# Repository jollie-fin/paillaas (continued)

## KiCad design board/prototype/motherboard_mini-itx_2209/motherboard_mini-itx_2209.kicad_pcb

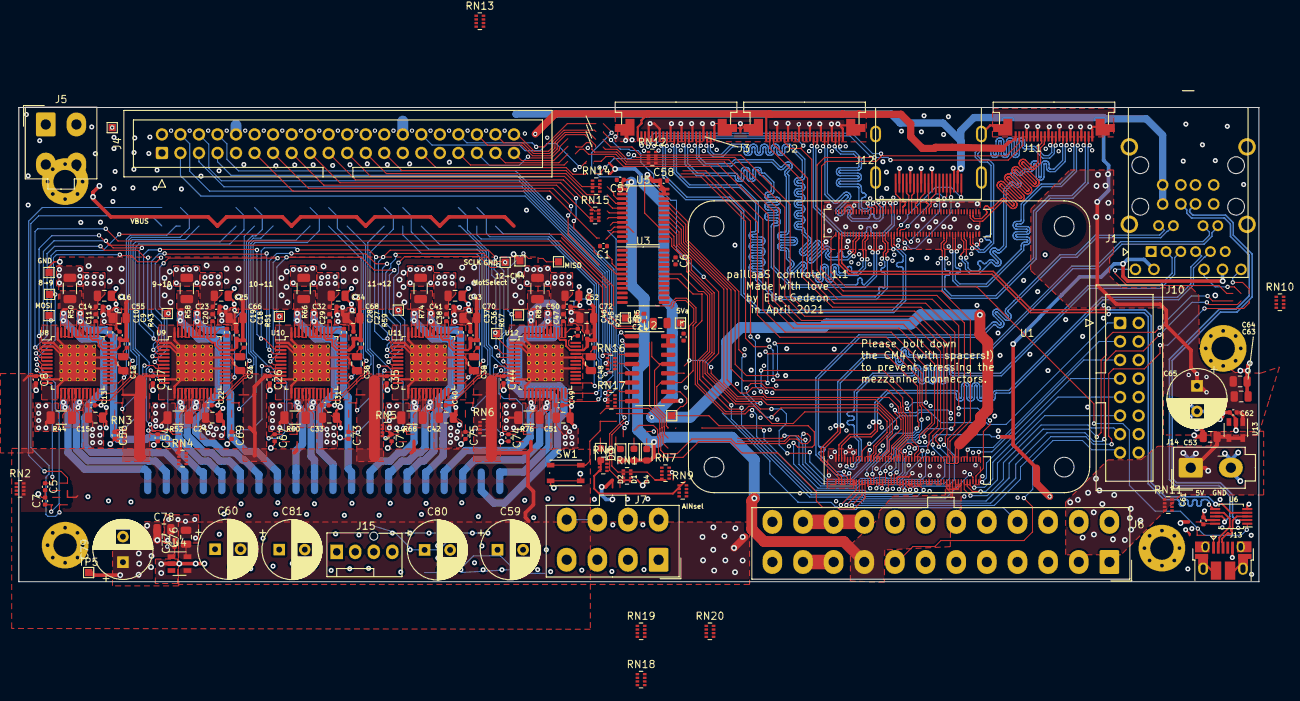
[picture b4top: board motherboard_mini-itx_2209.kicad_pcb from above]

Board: 4 copper layers, 170.0 x 65.0 mm, 167 parts (0 on the bottom side), 219 nets.

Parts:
C1, C2, C3, C6, C8, C9, C11, C13, C14, C17, C18, C20, C22, C23, C26, C27, C29, C31, C32, C35, C36, C38, C40, C41, C44, C45, C47, C49, C50, C57, C58, C61, C62, C77: 100n; C_0402_1005Metric
C4, C12, C15, C16, C21, C24, C25, C30, C33, C34, C39, C42, C43, C48, C51, C52, C53, C55, C63, C64, C66, C68, C70, C72, C76, C78: 10u; C_0805_2012Metric
C5, C7, C54, C56, C67, C69, C71, C73, C74, C75: 1n; C_0402_1005Metric
C10, C19, C28, C37, C46: 22n; C_0402_1005Metric
C59, C60, C65, C79, C80, C81: 100u; CP_Radial_D8.0mm_P3.50mm
D1, D2, D3, D4: RED; LED_0603_1608Metric
H1, H2, H3, H4: 4mm; MountingHole_3.2mm_M3_Pad_Via
J1: RJMG2310228A0ER
J2, J3, J11: Conn_01x22_MountingPin; SFV22R-1STBE1HLF
J4: Conn_02x20_Odd_Even; IDC-Header_2x20_P2.54mm_Vertical
J5: Conn_01x04_Female; Molex_Mini-Fit_Jr_5566-04A_2x02_P4.20mm_Vertical
J6: ATX24pin; Molex_Mini-Fit_Jr_5566-24A_2x12_P4.20mm_Vertical
J7: ATXP8; Molex_Mini-Fit_Jr_5566-08A_2x04_P4.20mm_Vertical
J10: Conn_02x08_Odd_Even; IDC-Header_2x08_P2.54mm_Vertical
J12: HDMI_A; HDMI_RAHHD19TR
J13: USB_B_Micro; USB_Micro-B_Amphenol_10103594-0001LF_Horizontal
J14: Conn_02x01; Molex_Mini-Fit_Jr_5566-02A_2x01_P4.20mm_Vertical
J15: Fan connector; FanPinHeader_1x04_P2.54mm_Vertical
R5, R43, R51, R59, R67, R75: 10; R_0402_1005Metric
R44, R50, R52, R58, R60, R66, R68, R74, R76, R82: 0R15; R_1206_3216Metric
RN1, RN2, RN3, RN4, RN5, RN6, RN7: 4x10k; R_Array_Concave_4x0402
RN8, RN9, RN10, RN11: 4x1k8; R_Array_Concave_4x0402
RN12, RN13, RN14, RN15, RN16, RN17: 4x150; R_Array_Concave_4x0402
RN18, RN19, RN20: 4x39; R_Array_Concave_4x0402
SW1: PTS526 SM15 SMTR2 LFS; SW_Push_1P1T_NO_Vertical_Wuerth_434133025816
TP1: 3V3a; TestPoint_Pad_1.0x1.0mm
TP2: AinSel; TestPoint_Pad_1.0x1.0mm
TP3, TP4, TP10: GND; TestPoint_Pad_1.0x1.0mm
TP5: 3V3bus; TestPoint_Pad_1.0x1.0mm
TP6: MISO; TestPoint_Pad_1.0x1.0mm
TP7: SCLK; TestPoint_Pad_1.0x1.0mm
TP8: MOSI; TestPoint_Pad_1.0x1.0mm
TP9: MotSel; TestPoint_Pad_1.0x1.0mm
TP11, TP13, TP15, TP17, TP19: Toright; TestPoint_Pad_1.0x1.0mm
TP12: 5Vbus; TestPoint_Pad_1.0x1.0mm
U1: Compute_Module_4_Functional; Raspberry-Pi-4-Compute-Module
U2: MCP3008; SOIC-16_3.9x9.9mm_P1.27mm
U3, U5: 74LVC4245A; TSSOP-24_4.4x7.8mm_P0.65mm
U4, U13: AP22804AW5; SOT-23-5
U6: FSUSB30MUX; MSOP-10_3x3mm_P0.5mm
U8, U9, U10, U11, U12: TMC5130A-TA; TQFP-48-1EP_7x7mm_P0.5mm_EP5x5mm_ThermalVias

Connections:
3V3bus: C77.1, C78.1, C79.1, J2.22, J3.22, J4.2, J4.32, J5.4, J11.22, TP5.1, U4.1
3V3mcu: C2.1, C6.1, C58.1, D3.2, R5.2, RN7.1, RN7.2, RN7.5, RN9.6, RN9.7, U1.78, U1.84, U1.86, U3.23, U3.24, U5.23, U5.24
5Vsb: C1.1, C57.1, D1.2, D2.2, D4.2, J6.9, U1.77, U1.79, U1.81, U1.83, U1.85, U1.87, U3.1, U3.2, U3.3, U3.4, U5.1
+3V3: C8.1, C17.1, C26.1, C35.1, C44.1, C76.1, J1.12, J1.14, J6.1, J6.2, J6.12, J6.13, RN2.1, RN2.4, RN3.1, RN3.4, RN4.1, RN4.4, RN5.1, RN5.4, RN6.1, RN6.4, RN19.1, U1.48, U4.4, U4.5, U8.10, U9.10, U10.10, U11.10, U12.10
+5V: C9.1, C18.1, C27.1, C36.1, C45.1, C53.1, C55.1, C66.1, C68.1, C70.1, C72.1, J6.4, J6.6, J6.21, J6.22, J6.23, J14.1, R43.1, R51.1, R59.1, R67.1, R75.1, RN1.1, U8.34, U8.39, U9.34, U9.39, U10.34, U10.39, U11.34, U11.39, U12.34, U12.39, U13.4, U13.5
+12V: C11.2, C13.1, C14.1, C15.1, C16.1, C20.2, C22.1, C23.1, C24.1, C25.1, C29.2, C31.1, C32.1, C33.1, C34.1, C38.2, C40.1, C41.1, C42.1, C43.1, C47.2, C49.1, C50.1, C51.1, C52.1, C59.1, C60.1, C80.1, C81.1, J7.5, J7.6, J7.7, J7.8, J15.2, RN1.3, RN1.4, U8.21, U8.40, U9.21, U9.40, U10.21, U10.40, U11.21, U11.40, U12.21, U12.40
/CAM_GPIO: J2.17, J3.17, U1.97
/GPIO/+3V3a: C3.1, C4.1, R5.1, TP1.1, U2.15, U2.16
/GPIO/ACT_LED: RN8.1, U1.21
/GPIO/AIN0: RN1.5, RN1.6, RN9.8, U2.1
/GPIO/AIN1: RN1.7, RN1.8, U2.2
/GPIO/AIN2: RN16.8, U2.3
/GPIO/AIN2P: J4.3, RN16.1
/GPIO/AIN3: RN16.7, U2.4
/GPIO/AIN3P: J4.4, RN16.2
/GPIO/AIN4: RN16.6, U2.5
/GPIO/AIN4P: J4.5, RN16.3
/GPIO/AIN5: RN16.5, U2.6
/GPIO/AIN5P: J4.6, RN16.4
/GPIO/AIN6: RN17.8, U2.7
/GPIO/AIN6P: J4.7, RN17.1
/GPIO/AIN7: RN17.7, U2.8
/GPIO/AIN7P: J4.8, RN17.2
/GPIO/AIN_SELECT_3V: TP2.1, U1.58, U2.10
/GPIO/CS6: U1.56, U5.18
/GPIO/CS6P: J4.19, RN15.2
/GPIO/CS6_5V: RN15.7, U5.6
/GPIO/GPIO8: RN13.7, U1.39
/GPIO/GPIO8P: J4.37, RN13.2
/GPIO/GPIO9: RN12.5, U1.40
/GPIO/GPIO9P: J4.40, RN12.4
/GPIO/GPIO10: RN12.6, U1.44
/GPIO/GPIO10P: J4.35, RN12.3
/GPIO/GPIO11: RN12.8, U1.38
/GPIO/GPIO11P: J4.34, RN12.1
/GPIO/GPIO16: RN13.8, U1.29
/GPIO/GPIO16P: J4.39, RN13.1
/GPIO/GPIO18: RN13.5, U1.49
/GPIO/GPIO18P: J4.38, RN13.4
/GPIO/GPIO24: RN13.6, U1.45
/GPIO/GPIO24P: J4.36, RN13.3
/GPIO/GPIO25: RN12.7, U1.41
/GPIO/GPIO25P: J4.33, RN12.2
/GPIO/LED_BTN: RN9.5, U1.50
/GPIO/MISO: RN7.7, RN18.8, RN20.5, TP6.1, U1.34
/GPIO/MISO6: U1.26, U3.19
/GPIO/MISO6P: J4.17, RN17.3
/GPIO/MISO6_5V: RN17.6, U3.5
/GPIO/MOSI: RN18.6, TP8.1, U2.11, U8.5
/GPIO/MOSI4_3V: RN18.3, U1.30
/GPIO/MOSI6: U1.27, U5.19
/GPIO/MOSI6P: J4.21, RN15.1
/GPIO/MOSI6_5V: RN15.8, U5.5
/GPIO/MOTOR_SELECT: RN18.5, TP9.1, U8.3, U9.3, U10.3, U11.3, U12.3
/GPIO/MOTOR_SELECT_3V: RN18.4, U1.54
/GPIO/POWERED: RN8.2, U5.9
/GPIO/PS_ON: J6.16, U5.8
/GPIO/PS_ON_3V: RN7.8, U1.24, U5.16
/GPIO/PWM0: U1.31, U5.20
/GPIO/PWM0P: J4.23, RN14.4
/GPIO/PWM0_5V: RN14.5, U5.4
/GPIO/PWM1: U1.28, U5.21
/GPIO/PWM1P: J4.25, RN14.3
/GPIO/PWM1_5V: RN14.6, U5.3
/GPIO/RxD0: U1.51, U3.18
/GPIO/RxD0P: J4.13, RN17.4
/GPIO/RxD0_5V: RN17.5, U3.6
/GPIO/SCL6: RN9.3, RN14.7, U1.47
/GPIO/SCL6P: J4.29, RN14.2
/GPIO/SCLK: RN18.7, TP7.1, U2.13, U8.4, U9.4, U10.4, U11.4, U12.4
/GPIO/SCLK4_3V: RN18.2, U1.37
/GPIO/SCLK6: U1.25, U5.17
/GPIO/SCLK6P: J4.15, RN15.3
/GPIO/SCLK6_5V: RN15.6, U5.7
/GPIO/SDA6: RN9.2, RN14.8, U1.46
/GPIO/SDA6P: J4.30, RN14.1
/GPIO/TxD0: U1.55, U5.14
/GPIO/TxD0P: J4.11, RN15.4
/GPIO/TxD0_5V: RN15.5, U5.10
/SCL0: J3.20, J11.20, U1.80
/SCL1: J2.20, U1.35
/SDA0: J3.21, J11.21, U1.82
/SDA1: J2.21, U1.36
/camera/CAM0C+: J2.9, U1.142
/camera/CAM0C-: J2.8, U1.140
/camera/CAM0D0+: J2.3, U1.130
/camera/CAM0D0-: J2.2, U1.128
/camera/CAM0D1+: J2.6, U1.136
/camera/CAM0D1-: J2.5, U1.134
/camera/CAM1C+: J3.9, U1.129
/camera/CAM1C-: J3.8, U1.127
/camera/CAM1D0+: J3.3, U1.117
/camera/CAM1D0-: J3.2, U1.115
/camera/CAM1D1+: J3.6, U1.123
/camera/CAM1D1-: J3.5, U1.121
/camera/CAM1D2+: J3.12, U1.135
/camera/CAM1D2-: J3.11, U1.133
/camera/CAM1D3+: J3.15, U1.141
/camera/CAM1D3-: J3.14, U1.139
/cm4/BT_disable: J10.11, U1.91
/cm4/EEPROMprotect: J10.1, U1.20
/cm4/Filtered_3V3: C61.1, RN19.5, RN19.6, U6.10
/cm4/HostDetection: RN11.1, RN11.2, U1.101, U6.1
/cm4/LED_Pwr: U1.95, U5.15
/cm4/PG: J6.8, J10.15
/cm4/USB_cm4+: U1.105, U6.4
/cm4/USB_cm4-: U1.103, U6.6
/cm4/USB_ext+: J1.U23, U6.2
/cm4/USB_ext-: J1.U22, U6.8
/cm4/USB_micro+: J13.3, U6.3
/cm4/USB_micro-: J13.2, U6.7
/cm4/WL_disable: J10.13, U1.89
/cm4/global_en: J10.7, U1.99
/cm4/nEXTRST: J10.5, U1.100
/cm4/rpireboot: J10.9, U1.93
/cm4/run_pg: J10.3, U1.92
/display/DSI1C+: J11.9, U1.189
/display/DSI1C-: J11.8, U1.187
/display/DSI1D0+: J11.3, U1.177
/display/DSI1D0-: J11.2, U1.175
/display/DSI1D1+: J11.6, U1.183
/display/DSI1D1-: J11.5, U1.181
/display/DSI1D2+: J11.12, U1.195
/display/DSI1D2-: J11.11, U1.193
/display/DSI1D3+: J11.15, U1.196
/display/DSI1D3-: J11.14, U1.194
/display/HDMI_0+: J12.7, U1.158
/display/HDMI_0-: J12.9, U1.160
/display/HDMI_1+: J12.4, U1.152
/display/HDMI_1-: J12.6, U1.154
/display/HDMI_2+: J12.1, U1.146
/display/HDMI_2-: J12.3, U1.148
/display/HDMI_C+: J12.10, U1.164
/display/HDMI_C-: J12.12, U1.166
/display/HDMI_CEC: J12.13, U1.149
/display/HDMI_HOT: J12.19, U1.143
/display/HDMI_SCL: J12.16, U1.147
/display/HDMI_SDA: J12.15, U1.145
/ethernet/ETH_0+: J1.2, U1.12
/ethernet/ETH_0-: J1.3, U1.10
/ethernet/ETH_1+: J1.4, U1.4
/ethernet/ETH_1-: J1.5, U1.6
/ethernet/ETH_2+: J1.7, U1.11
/ethernet/ETH_2-: J1.8, U1.9
/ethernet/ETH_3+: J1.9, U1.3
/ethernet/ETH_3-: J1.10, U1.5
/ethernet/ETH_LED_green: RN10.2, U1.17
/ethernet/ETH_LED_orange: RN10.3, U1.19
/ethernet/ETH_LED_yellow: RN10.1, U1.15
/powerIO/8LIML: RN2.7, RN2.8
/powerIO/8LIMR: RN2.5, RN2.6
/powerIO/9LIML: RN3.7, RN3.8
/powerIO/9LIMR: RN3.5, RN3.6
/powerIO/10LIML: RN4.7, RN4.8
/powerIO/10LIMR: RN4.5, RN4.6
/powerIO/11LIML: RN5.7, RN5.8
/powerIO/11LIMR: RN5.5, RN5.6
/powerIO/12LIML: RN6.7, RN6.8
/powerIO/12LIMR: RN6.5, RN6.6
/powerIO/motorU8/BRA: R50.1, U8.44
/powerIO/motorU8/BRB: R44.1, U8.17
/powerIO/motorU8/CPI: C10.1, U8.37
/powerIO/motorU8/CPO: C10.2, U8.35
/powerIO/motorU8/FILTERED_5V: C12.2, R43.2, U8.33
/powerIO/motorU8/LIMITL_RAW: C7.1, RN2.2, U8.8
/powerIO/motorU8/LIMITR_RAW: C5.1, RN2.3, U8.9
/powerIO/motorU8/MISO: TP11.1, U8.7, U9.5
/powerIO/motorU8/VCP: C11.1, U8.38
/powerIO/motorU9/BRA: R58.1, U9.44
/powerIO/motorU9/BRB: R52.1, U9.17
/powerIO/motorU9/CPI: C19.1, U9.37
/powerIO/motorU9/CPO: C19.2, U9.35
/powerIO/motorU9/FILTERED_5V: C21.2, R51.2, U9.33
/powerIO/motorU9/LIMITL_RAW: C56.1, RN3.2, U9.8
/powerIO/motorU9/LIMITR_RAW: C54.1, RN3.3, U9.9
/powerIO/motorU9/MISO: TP13.1, U9.7, U10.5
/powerIO/motorU9/VCP: C20.1, U9.38
/powerIO/motorU10/BRA: R66.1, U10.44
/powerIO/motorU10/BRB: R60.1, U10.17
/powerIO/motorU10/CPI: C28.1, U10.37
/powerIO/motorU10/CPO: C28.2, U10.35
/powerIO/motorU10/FILTERED_5V: C30.2, R59.2, U10.33
/powerIO/motorU10/LIMITL_RAW: C69.1, RN4.2, U10.8
/powerIO/motorU10/LIMITR_RAW: C67.1, RN4.3, U10.9
/powerIO/motorU10/MISO: TP15.1, U10.7, U11.5
/powerIO/motorU10/VCP: C29.1, U10.38
/powerIO/motorU11/BRA: R74.1, U11.44
/powerIO/motorU11/BRB: R68.1, U11.17
/powerIO/motorU11/CPI: C37.1, U11.37
/powerIO/motorU11/CPO: C37.2, U11.35
/powerIO/motorU11/FILTERED_5V: C39.2, R67.2, U11.33
/powerIO/motorU11/LIMITL_RAW: C73.1, RN5.2, U11.8
/powerIO/motorU11/LIMITR_RAW: C71.1, RN5.3, U11.9
/powerIO/motorU11/MISO: TP17.1, U11.7, U12.5
/powerIO/motorU11/VCP: C38.1, U11.38
/powerIO/motorU12/BRA: R82.1, U12.44
/powerIO/motorU12/BRB: R76.1, U12.17
/powerIO/motorU12/CPI: C46.1, U12.37
/powerIO/motorU12/CPO: C46.2, U12.35
/powerIO/motorU12/FILTERED_5V: C48.2, R75.2, U12.33
/powerIO/motorU12/LIMITL_RAW: C75.1, RN6.2, U12.8
/powerIO/motorU12/LIMITR_RAW: C74.1, RN6.3, U12.9
/powerIO/motorU12/MISO: RN20.4, TP19.1, U12.7
/powerIO/motorU12/VCP: C47.1, U12.38
GND: C1.2, C2.2, C3.2, C4.2, C5.2, C6.2, C7.2, C8.2, C9.2, C12.1, C13.2, C14.2, C15.2, C16.2, C17.2, C18.2, C21.1, C22.2, C23.2, C24.2, C25.2, C26.2, C27.2, C30.1, C31.2, C32.2, C33.2, C34.2, C35.2, C36.2, C39.1, C40.2, C41.2, C42.2, C43.2, C44.2, C45.2, C48.1, C49.2, C50.2, C51.2, C52.2, C53.2, C54.2, C55.2, C56.2, C57.2, C58.2, C59.2, C60.2, C61.2, C62.2, C63.2, C64.2, C65.2, C66.2, C67.2, C68.2, C69.2, C70.2, C71.2, C72.2, C73.2, C74.2, C75.2, C76.2, C77.2, C78.2, C79.2, C80.2, C81.2, H1.1, H2.1, H3.1, H4.1, J1.1, J1.SH, J1.U14, J1.U24, J2.1, J2.4, J2.7, J2.10, J2.13, J2.16, J2.19, J2.MP, J3.1, J3.4, J3.7, J3.10, J3.13, J3.16, J3.19, J3.MP, J4.1, J4.9, J4.12, J4.14, J4.16, J4.18, J4.20, J4.22, J4.24, J4.26, J4.27, J4.31, J5.2, J5.3, J6.3, J6.5, J6.7, J6.15, J6.17, J6.18, J6.19, J6.24, J7.1, J7.2, J7.3, J7.4, J10.2, J10.4, J10.6, J10.8, J10.10, J10.12, J10.14, J10.16, J11.1, J11.4, J11.7, J11.10, J11.13, J11.16, J11.19, J11.MP, J12.2, J12.5, J12.8, J12.11, J12.17, J12.SH, J13.5, J13.6, J14.2, J15.1, R44.2, R50.2, R52.2, R58.2, R60.2, R66.2, R68.2, R74.2, R76.2, R82.2, RN1.2, RN8.3, RN9.1, RN11.7, SW1.2, TP3.1, TP4.1, TP10.1, U1.1, U1.2, U1.7, U1.8, U1.13, U1.14, U1.22, U1.23, U1.32, U1.33, U1.42, U1.43, U1.52, U1.53, U1.59, U1.60, U1.65, U1.66, U1.71, U1.74, U1.98, U1.107, U1.108, U1.113, U1.114, U1.119, U1.120, U1.125, U1.126, U1.131, U1.132, U1.137, U1.138, U1.144, U1.150, U1.155, U1.156, U1.161, U1.162, U1.167, U1.168, U1.173, U1.174, U1.179, U1.180, U1.185, U1.186, U1.191, U1.192, U1.197, U1.198, U2.9, U2.14, U3.7, U3.8, U3.9, U3.10, U3.11, U3.12, U3.13, U3.22, U4.2, U5.2, U5.11, U5.12, U5.13, U5.22, U6.5, U6.9, U8.1, U8.2, U8.11, U8.13, U8.29, U8.32, U8.48, U8.49, U9.1, U9.2, U9.11, U9.13, U9.29, U9.32, U9.48, U9.49, U10.1, U10.2, U10.11, U10.13, U10.29, U10.32, U10.48, U10.49, U11.1, U11.2, U11.11, U11.13, U11.29, U11.32, U11.48, U11.49, U12.1, U12.2, U12.11, U12.13, U12.29, U12.32, U12.48, U12.49, U13.2
unnamed: D1.1, RN8.8
unnamed: D2.1, RN8.7
unnamed: D3.1, RN8.5
unnamed: D4.1, RN8.6
unnamed: J1.11, RN10.8
unnamed: J1.13, RN10.7
unnamed: J1.15, RN10.6
unnamed: J6.10, J6.11
unnamed: J13.1, RN11.8
unnamed: RN7.4, RN8.4, RN9.4, SW1.1
unnamed: RN18.1, U2.12
unnamed: RN19.2, RN19.3, RN19.4
unnamed: RN19.7, RN19.8
VBUS: C62.1, C63.1, C64.1, C65.1, J1.U11, J1.U21, J4.10, J4.28, J5.1, J12.18, TP12.1, U13.1

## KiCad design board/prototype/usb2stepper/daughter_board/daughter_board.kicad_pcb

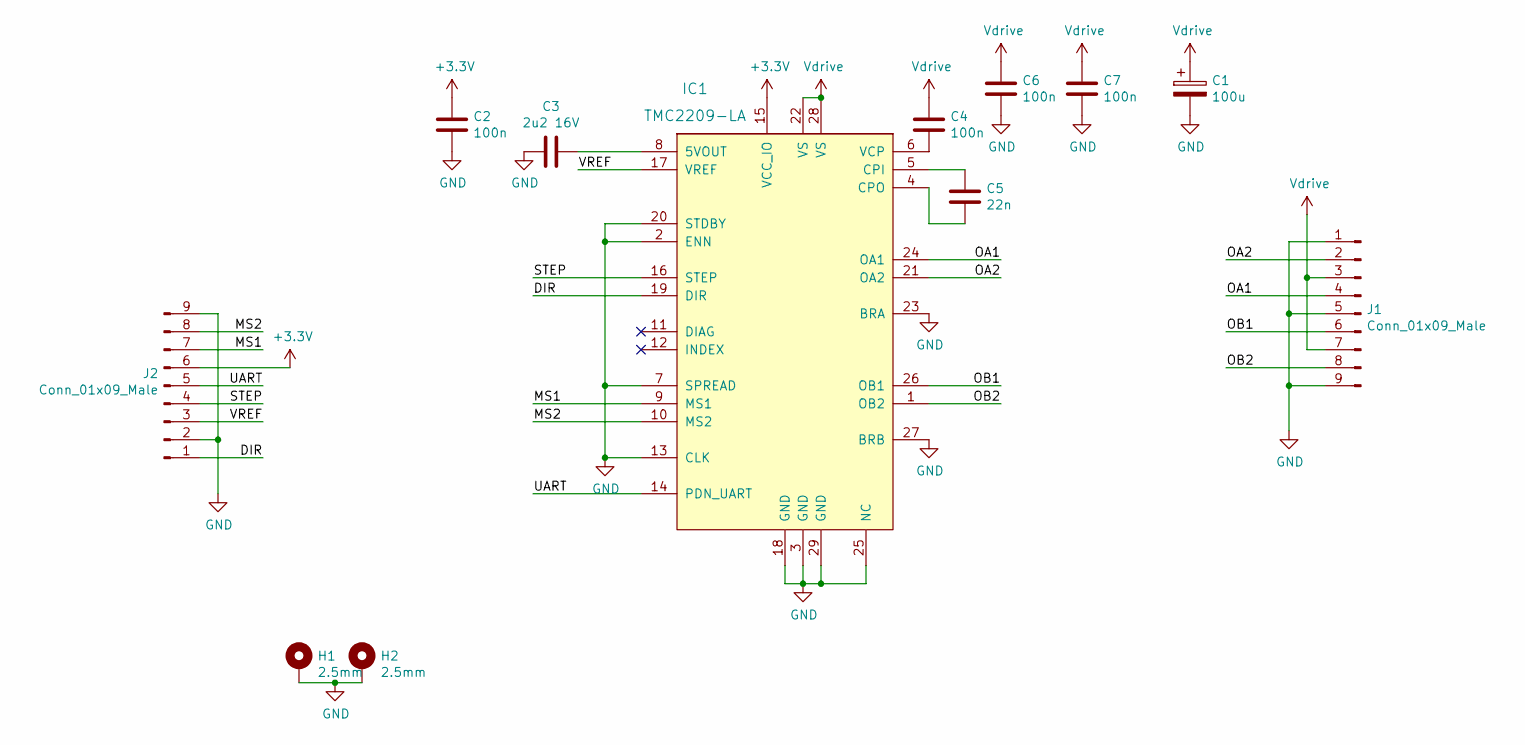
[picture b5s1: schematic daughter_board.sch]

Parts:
C1: 100u; CP_Elec_5x4.5
C2, C4, C6, C7: 100n; C_0402
C3: 2u2 16V; C_0402
C5: 22n; C_0402
H1, H2: 2.5mm; MountingHole_2.2mm_M2_ISO7380_Pad
IC1: TMC2209-LA; QFN-28-1EP_5x5mm_Pitch0.5mm_EP3.7x3.7
J1, J2: Conn_01x09_Male; Pin_Header_Straight_1x09_Pitch2.54mm_SMD_Pin1Left

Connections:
+3V3: C2.2, IC1.15 (VCC_IO), J2.6
/DIR: IC1.19 (DIR), J2.1
/MS1: IC1.9 (MS1), J2.7
/MS2: IC1.10 (MS2), J2.8
/OA1: IC1.24 (OA1), J1.4
/OA2: IC1.21 (OA2), J1.2
/OB1: IC1.26 (OB1), J1.6
/OB2: IC1.1 (OB2), J1.8
/STEP: IC1.16 (STEP), J2.4
/UART: IC1.14 (PDN_UART), J2.5
/VREF: IC1.17 (VREF), J2.3
GND: C1.2, C2.1, C3.2, C6.1, C7.1, H1.1, H2.1, IC1.2 (ENN), IC1.3 (GND), IC1.7 (SPREAD), IC1.13 (CLK), IC1.18 (GND), IC1.20 (STDBY), IC1.23 (BRA), IC1.25 (NC), IC1.27 (BRB), IC1.29 (GND), J1.1, J1.5, J1.9, J2.2, J2.9
unnamed: C3.1, IC1.8 (5VOUT)
unnamed: C4.1, IC1.6 (VCP)
unnamed: C5.1, IC1.5 (CPI)
unnamed: C5.2, IC1.4 (CPO)
Vdrive: C1.1, C4.2, C6.2, C7.2, IC1.22 (VS), IC1.28 (VS), J1.3, J1.7

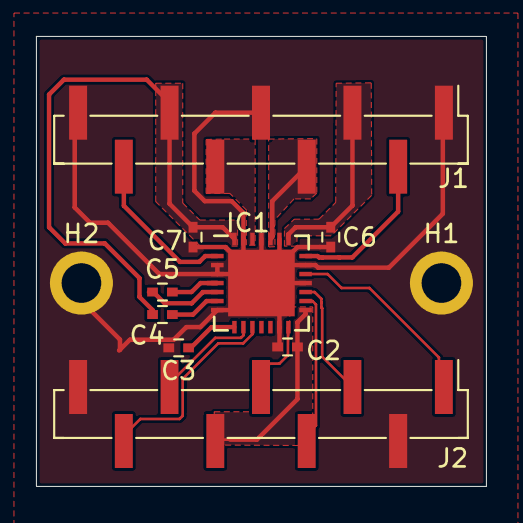
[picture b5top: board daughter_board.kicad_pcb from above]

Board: 2 copper layers, 25.0 x 25.0 mm, 11 parts (0 on the bottom side), 17 nets.

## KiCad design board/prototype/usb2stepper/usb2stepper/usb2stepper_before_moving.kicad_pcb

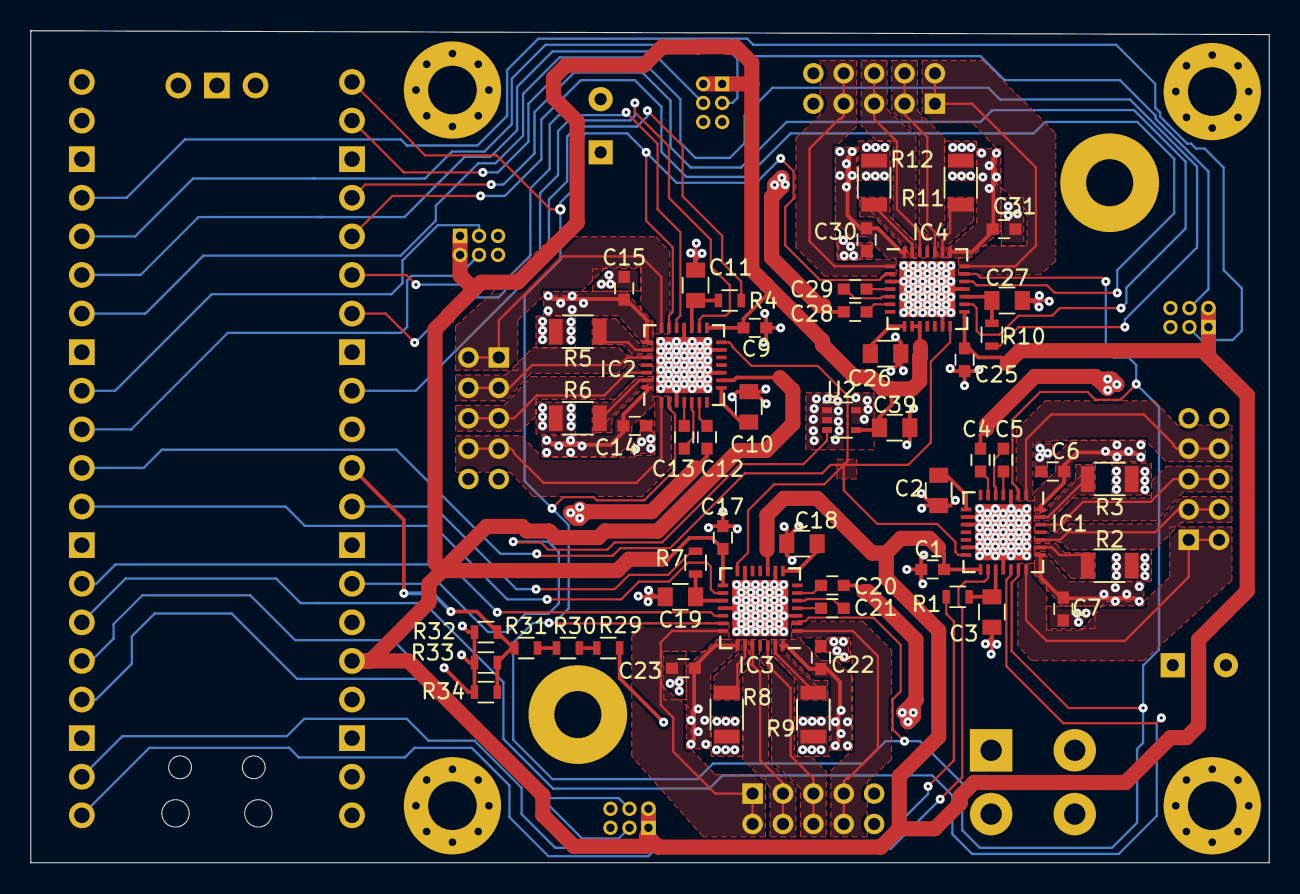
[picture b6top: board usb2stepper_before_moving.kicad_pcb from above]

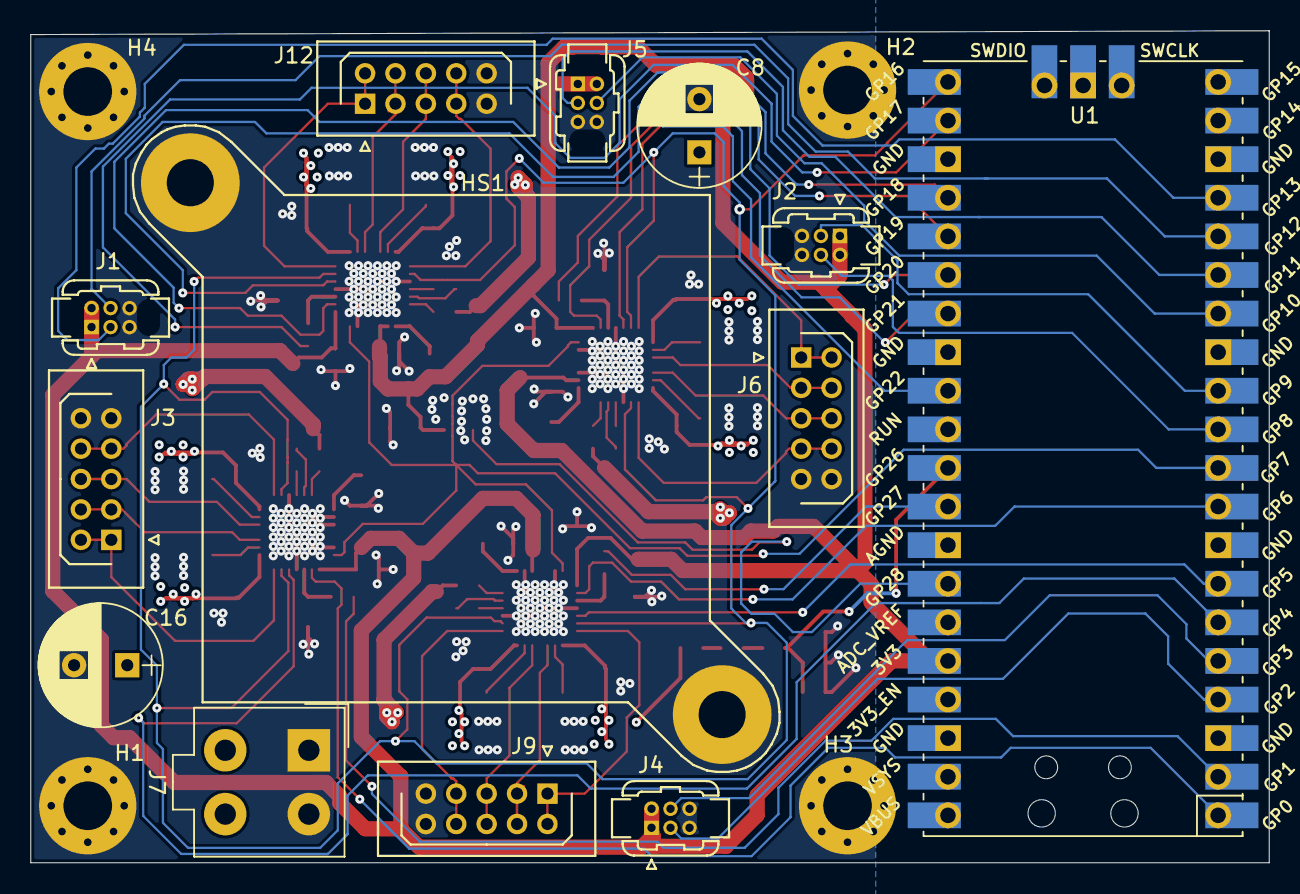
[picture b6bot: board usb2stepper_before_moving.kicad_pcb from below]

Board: 4 copper layers, 81.5 x 54.8 mm, 69 parts (17 on the bottom side), 73 nets.

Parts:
C1, C4, C6, C7, C9, C12, C14, C15, C17, C20, C22, C23, C25, C28, C30, C31: 100n; C_0603
C2, C3, C10, C11, C18, C19, C26, C27, C39: 2u2 16V; C_0805
C5, C13, C21, C29: 22n; C_0603
C8, C16: 100uF; CP_Radial_D8.0mm_P3.50mm
H1, H2, H3, H4: 3mm; MountingHole_3.2mm_M3_Pad_Via
HS1: 30x30mm; PCB_Heatsink_30x30mm_2xFixation3mm
IC1, IC2, IC3, IC4: TMC2209-LA; QFN-28-1EP_5x5mm_Pitch0.5mm_EP3.7x3.7
J1, J2, J4, J5: Conn_02x03_Odd_Even; Harwin_Gecko-G125-MVX0605L1X_2x03x1.25mm_Straight
J3, J6, J9, J12: Conn_02x05_Odd_Even; Harwin_LTek-Male_2x05x2.00mm_Straight
J7: Minifit_jr_2x2; Molex_MiniFit-JR-5556-04A_2x02x4.20mm_Straight
R1, R4, R7, R10, R29, R30, R31, R32, R33, R34: 10k; R_0603
R2, R3, R5, R6, R8, R9, R11, R12: 0.1; R_1206
U1: Pico; RPi_Pico_SMD_TH
U2: MCP9700AT-ELT; SOT-353_SC-70-5

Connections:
+3V3: C1.1, C9.1, C17.1, C25.1, C39.1, IC1.15, IC2.9, IC2.15, IC3.10, IC3.15, IC4.9, IC4.10, IC4.15, J1.1, J1.2, J2.1, J2.2, J4.1, J4.2, J5.1, J5.2, U1.36, U2.4
/24V_measure: R31.1, R32.2, R33.2, R34.2, U1.31
/DIR0: IC1.19, U1.6
/DIR1: IC2.19, U1.26
/DIR2: IC3.19, U1.7
/DIR3: IC4.19, U1.25
/DISABLE_MOT: IC1.2, IC1.20, IC2.2, IC2.20, IC3.2, IC3.20, IC4.2, IC4.20, U1.21
/REFL0: J1.3, U1.17
/REFL1: J2.3, U1.12
/REFL2: J4.3, U1.4
/REFL3: J5.3, U1.15
/REFR0: J1.4, U1.16
/REFR1: J2.4, U1.11
/REFR2: J4.4, U1.5
/REFR3: J5.4, U1.14
/STEP0: IC1.16, U1.1
/STEP1: IC2.16, U1.27
/STEP2: IC3.16, U1.9
/STEP3: IC4.16, U1.24
/Sheet608F6F9E/BRA: IC1.23, R2.2
/Sheet608F6F9E/BRB: IC1.27, R3.2
/Sheet608F6F9E/OA1: IC1.24, J3.3, J3.4
/Sheet608F6F9E/OA2: IC1.21, J3.1, J3.2
/Sheet608F6F9E/OB1: IC1.26, J3.5, J3.6
/Sheet608F6F9E/OB2: IC1.1, J3.7, J3.8
/Sheet608F6F9E/Vref: C3.1, IC1.17, R1.1
/TEMP: U1.34, U2.3
/UART: IC1.14, IC2.14, IC3.14, IC4.14, U1.10
/VREF_PWM0: R1.2, U1.2
/VREF_PWM1: R4.2, U1.29
/VREF_PWM2: R7.2, U1.32
/VREF_PWM3: R10.2, U1.22
/sheet6092AD70/BRA: IC4.23, R11.2
/sheet6092AD70/BRB: IC4.27, R12.2
/sheet6092AD70/OA1: IC4.24, J12.3, J12.4
/sheet6092AD70/OA2: IC4.21, J12.1, J12.2
/sheet6092AD70/OB1: IC4.26, J12.5, J12.6
/sheet6092AD70/OB2: IC4.1, J12.7, J12.8
/sheet6092AD70/Vref: C27.1, IC4.17, R10.1
/sheet609275BA/BRA: IC2.23, R5.2
/sheet609275BA/BRB: IC2.27, R6.2
/sheet609275BA/OA1: IC2.24, J6.3, J6.4
/sheet609275BA/OA2: IC2.21, J6.1, J6.2
/sheet609275BA/OB1: IC2.26, J6.5, J6.6
/sheet609275BA/OB2: IC2.1, J6.7, J6.8
/sheet609275BA/Vref: C11.1, IC2.17, R4.1
/sheet60929021/BRA: IC3.23, R8.2
/sheet60929021/BRB: IC3.27, R9.2
/sheet60929021/OA1: IC3.24, J9.3, J9.4
/sheet60929021/OA2: IC3.21, J9.1, J9.2
/sheet60929021/OB1: IC3.26, J9.5, J9.6
/sheet60929021/OB2: IC3.1, J9.7, J9.8
/sheet60929021/Vref: C19.1, IC3.17, R7.1
GND: C1.2, C2.2, C3.2, C6.2, C7.2, C8.2, C9.2, C10.2, C11.2, C14.2, C15.2, C16.2, C17.2, C18.2, C19.2, C22.2, C23.2, C25.2, C26.2, C27.2, C30.2, C31.2, C39.2, H1.1, H2.1, H3.1, H4.1, HS1.1, HS1.2, HS1.3, IC1.3, IC1.9, IC1.10, IC1.13, IC1.18, IC1.29, IC2.3, IC2.10, IC2.13, IC2.18, IC2.29, IC3.3, IC3.9, IC3.13, IC3.18, IC3.29, IC4.3, IC4.13, IC4.18, IC4.29, J1.5, J1.6, J2.5, J2.6, J3.9, J3.10, J4.5, J4.6, J5.5, J5.6, J6.9, J6.10, J7.1, J7.2, J9.9, J9.10, J12.9, J12.10, R2.1, R3.1, R5.1, R6.1, R8.1, R9.1, R11.1, R12.1, R32.1, R33.1, R34.1, U1.3, U1.8, U1.13, U1.18, U1.23, U1.28, U1.33, U1.38, U1.42, U2.1, U2.2, U2.5
unnamed: C2.1, IC1.8
unnamed: C4.2, IC1.6
unnamed: C5.1, IC1.5
unnamed: C5.2, IC1.4
unnamed: C10.1, IC2.8
unnamed: C12.2, IC2.6
unnamed: C13.1, IC2.5
unnamed: C13.2, IC2.4
unnamed: C18.1, IC3.8
unnamed: C20.2, IC3.6
unnamed: C21.1, IC3.5
unnamed: C21.2, IC3.4
unnamed: C26.1, IC4.8
unnamed: C28.2, IC4.6
unnamed: C29.1, IC4.5
unnamed: C29.2, IC4.4
unnamed: R29.1, R30.2
unnamed: R30.1, R31.2
Vdrive: C4.1, C6.1, C7.1, C8.1, C12.1, C14.1, C15.1, C16.1, C20.1, C22.1, C23.1, C28.1, C30.1, C31.1, IC1.22, IC1.28, IC2.22, IC2.28, IC3.22, IC3.28, IC4.22, IC4.28, J7.3, J7.4, R29.2

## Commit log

2024-02-27 Improving readme
2024-02-28 Upgrading README.md
